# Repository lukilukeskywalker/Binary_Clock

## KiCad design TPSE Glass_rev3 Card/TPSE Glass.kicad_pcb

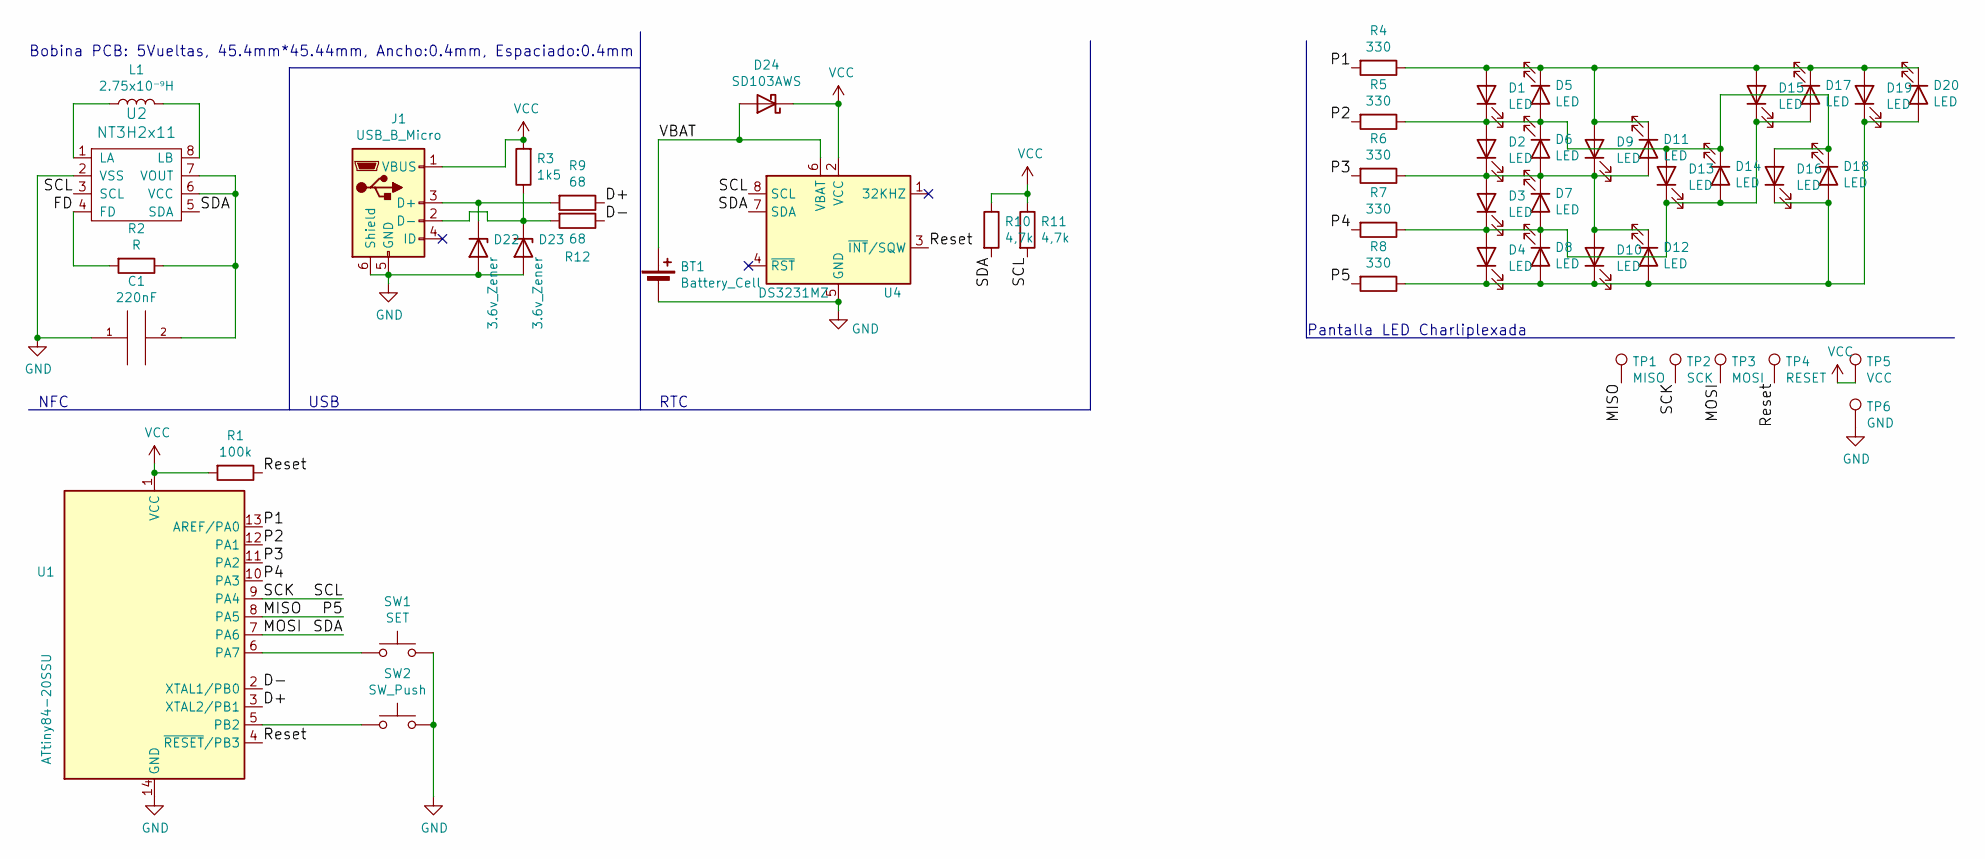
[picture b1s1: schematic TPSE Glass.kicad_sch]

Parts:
BT1: Battery_Cell; TE_796136-1
C1: 220nF; C_1210_3225Metric_Pad1.42x2.65mm_HandSolder
D1, D2, D3, D4, D5, D6, D7, D8, D9, D10, D11, D12, D13, D14, D15, D16, D17, D18, D19, D20: LED; LED_1206_3216Metric-ThroughPCB
D22, D23: 3.6v_Zener; D_SMA
D24: SD103AWS; D_SMA
J1: USB_B_Micro; TE_1981568-1
L1: 2.75x10⁻⁹H
R1: 100k; R_1206_3216Metric
R2: R; R_1206_3216Metric
R3: 1k5; R_1206_3216Metric
R4, R5, R6, R7, R8: 330; R_1206_3216Metric
R9, R12: 68; R_1206_3216Metric
R10, R11: 4,7k; R_1206_3216Metric
SW1: SET; SW_PTS526_SM08_SMTR2_LFS
SW2: SW_Push; SW_PTS526_SM08_SMTR2_LFS
TP1: MISO; TestPoint_Pad_D1.5mm
TP2: SCK; TestPoint_Pad_D1.5mm
TP3: MOSI; TestPoint_Pad_D1.5mm
TP4: RESET; TestPoint_Pad_D1.5mm
TP5: VCC; TestPoint_Pad_D1.5mm
TP6: GND; TestPoint_Pad_D1.5mm
U1: ATtiny84-20SSU; SOIC-14_3.9x8.7mm_P1.27mm
U2: NT3H2x11; TSSOP-8_3x3mm_P0.65mm
U4: DS3231MZ; SOIC-8_3.9x4.9mm_P1.27mm

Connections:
/D+: R9.1, U1.3 (XTAL2/PB1)
/D-: R12.1, U1.2 (XTAL1/PB0)
/FD: R2.2, U2.4 (FD)
/MISO: R8.2, TP1.1, U1.8 (PA5)
/MOSI: R10.2, TP3.1, U1.7 (PA6), U2.5 (SDA), U4.7 (SDA)
/P1: R4.2, U1.13 (AREF/PA0)
/P2: R5.2, U1.12 (PA1)
/P3: R6.2, U1.11 (PA2)
/P4: R7.2, U1.10 (PA3)
/Reset: R1.1, TP4.1, U1.4 (~RESET/PB3), U4.3 (~INT/SQW)
/SCK: R11.2, TP2.1, U1.9 (PA4), U2.3 (SCL), U4.8 (SCL)
/VBAT: BT1.1 (+), D24.2 (A), U4.6 (VBAT)
GND: BT1.2 (-), C1.1, D22.2 (A), D23.2 (A), J1.5 (GND), J1.6 (Shield), SW1.2, SW2.2, TP6.1, U1.14 (GND), U2.2 (VSS), U4.5 (GND)
unnamed: C1.2, R2.1, U2.6 (VCC), U2.7 (VOUT)
unnamed: D1.1 (K), D2.2 (A), D5.2 (A), D6.1 (K), D13.2 (A), D14.1 (K), D16.2 (A), D18.1 (K), R5.1
unnamed: D1.2 (A), D5.1 (K), D9.2 (A), D11.1 (K), D15.2 (A), D17.1 (K), D19.2 (A), D20.1 (K), R4.1
unnamed: D4.1 (K), D8.2 (A), D10.1 (K), D12.2 (A), D16.1 (K), D18.2 (A), D19.1 (K), D20.2 (A), R8.1
unnamed: D2.1 (K), D3.2 (A), D6.2 (A), D7.1 (K), D9.1 (K), D10.2 (A), D11.2 (A), D12.1 (K), R6.1
unnamed: D3.1 (K), D4.2 (A), D7.2 (A), D8.1 (K), D13.1 (K), D14.2 (A), D15.1 (K), D17.2 (A), R7.1
unnamed: D22.1 (K), J1.3 (D+), R9.2
unnamed: D23.1 (K), J1.2 (D-), R3.1, R12.2
unnamed: L1.1, U2.1 (LA)
unnamed: L1.2, U2.8 (LB)
unnamed: SW1.1, U1.6 (PA7)
unnamed: SW2.1, U1.5 (PB2)
VCC: D24.1 (K), J1.1 (VBUS), R1.2, R3.2, R10.1, R11.1, TP5.1, U1.1 (VCC), U4.2 (VCC)

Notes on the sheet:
Bobina PCB: 5Vueltas, 45.4mm*45.44mm, Ancho:0.4mm, Espaciado:0.4mm
NFC
USB
Pantalla LED Charliplexada
RTC

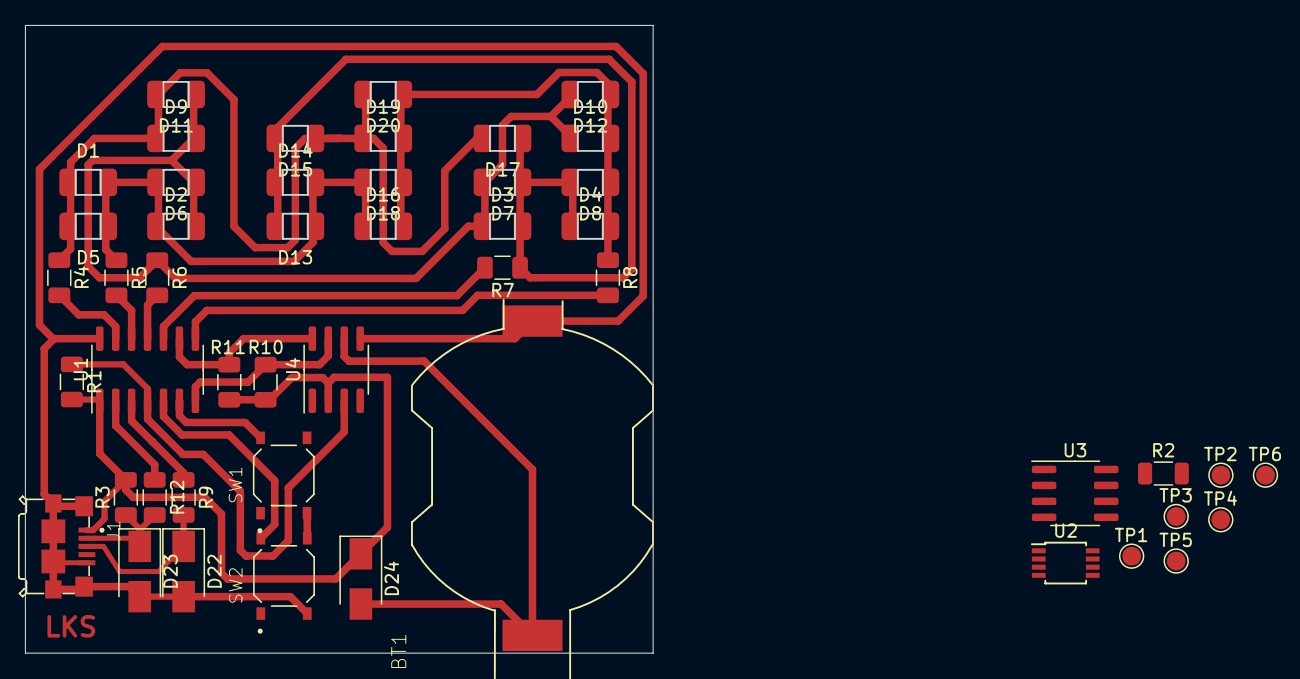
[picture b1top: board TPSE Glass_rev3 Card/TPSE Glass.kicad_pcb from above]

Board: 2 copper layers, 50.0 x 50.0 mm, 49 parts (0 on the bottom side), 24 nets.

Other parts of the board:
U3: PCF8563T; SOIC-8_3.9x4.9mm_P1.27mm

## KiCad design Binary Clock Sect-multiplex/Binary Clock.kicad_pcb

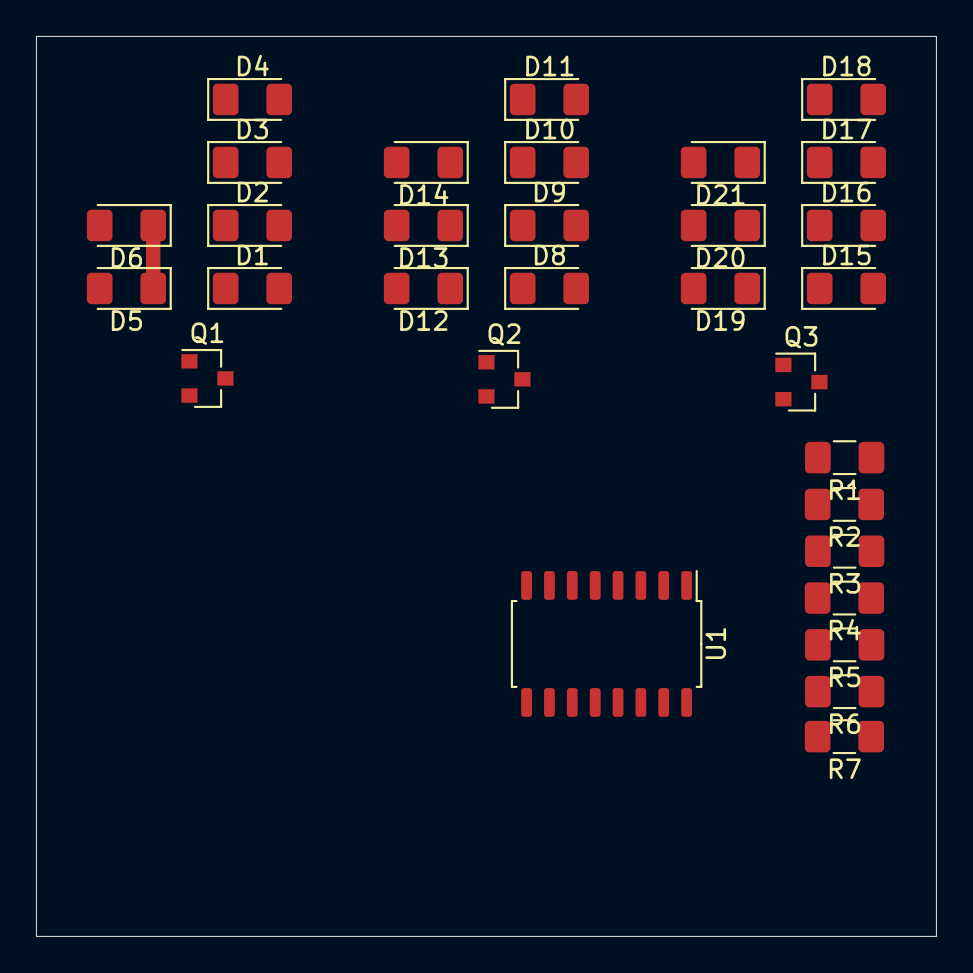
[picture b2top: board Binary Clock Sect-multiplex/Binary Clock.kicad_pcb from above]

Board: 2 copper layers, 50.0 x 50.0 mm, 31 parts (0 on the bottom side), 18 nets.

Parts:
D1, D2, D3, D4, D5, D6, D8, D9, D10, D11, D12, D13, D14, D15, D16, D17, D18, D19, D20, D21: LED; LED_1206_3216Metric_Pad1.42x1.75mm_HandSolder
Q1, Q2, Q3: BC847; SOT-23
R1, R2, R3, R4, R5, R6, R7: R; R_1206_3216Metric_Pad1.42x1.75mm_HandSolder
U1: 74HC595; SOP-16_4.55x10.3mm_P1.27mm

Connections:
/L0: D1.2, D8.2, D15.2, R1.1
/L1: D2.2, D9.2, D16.2, R2.1
/L2: D3.2, D10.2, D17.2, R3.1
/L3: D4.2, D11.2, D18.2, R4.1
/L4: D5.2, D12.2, D19.2, R5.1
/L5: D6.2, D13.2, D20.2, R6.1
/L6: D14.2, D21.2, R7.1
GND: Q1.2, Q2.2, Q3.2, U1.8
unnamed: D1.1, D2.1, D3.1, D4.1, D5.1, D6.1, Q1.3
unnamed: D8.1, D9.1, D10.1, D11.1, D12.1, D13.1, D14.1, Q2.3
unnamed: D15.1, D16.1, D17.1, D18.1, D19.1, D20.1, D21.1, Q3.3
unnamed: R1.2, U1.15
unnamed: R2.2, U1.1
unnamed: R3.2, U1.2
unnamed: R4.2, U1.3
unnamed: R5.2, U1.4
unnamed: R6.2, U1.5
unnamed: R7.2, U1.6

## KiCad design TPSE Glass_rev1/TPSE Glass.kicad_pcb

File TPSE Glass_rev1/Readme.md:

# Revision 1 Details

uC: Atmega32u4
RTC: DS3231 16-SOIC

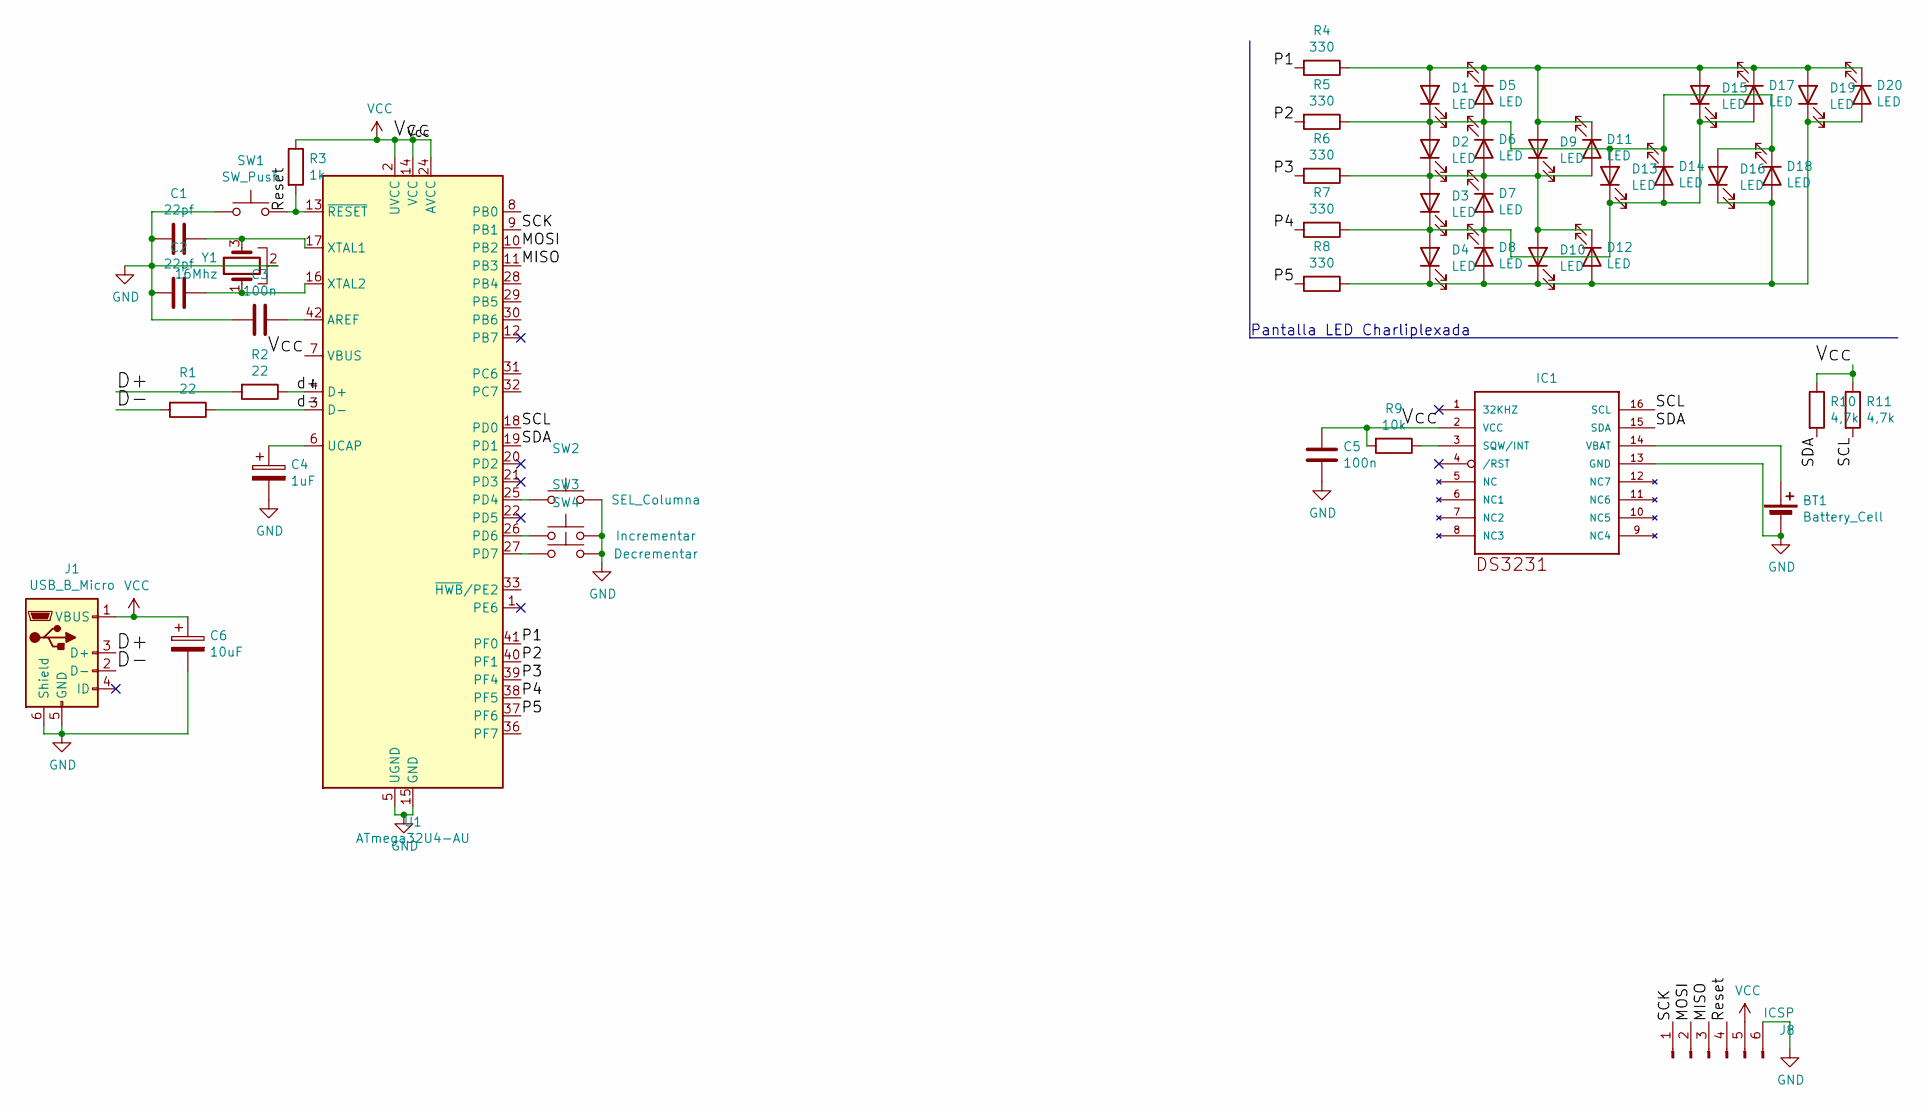
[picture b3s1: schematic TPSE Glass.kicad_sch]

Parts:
BT1: Battery_Cell; LINX CR2032 Holder
C1, C2: 22pf; C_0805_2012Metric_Pad1.15x1.40mm_HandSolder
C3, C5: 100n; C_0805_2012Metric
C4: 1uF; C_0603_1608Metric_Pad1.05x0.95mm_HandSolder
C6: 10uF; CP_EIA-1608-08_AVX-J
D1, D2, D3, D4, D5, D6, D7, D8, D9, D10, D11, D12, D13, D14, D15, D16, D17, D18, D19, D20: LED; LED_1206_3216Metric
IC1: DS3231; SO16W
J1: USB_B_Micro; USB_Micro-B_Molex_47346-0001
J8: ICSP; ICSP_SMD_Conn
R1, R2: 22; R_1206_3216Metric
R3: 1k; R_1206_3216Metric
R4, R5, R6, R7, R8: 330; R_1206_3216Metric
R9: 10k; R_1206_3216Metric
R10, R11: 4,7k; R_1206_3216Metric
SW1: SW_Push; SW_PTS526_SM08_SMTR2_LFS
SW2: SEL_Columna; SW_PTS526_SM08_SMTR2_LFS
SW3: Incrementar; SW_PTS526_SM08_SMTR2_LFS
SW4: Decrementar; SW_PTS526_SM08_SMTR2_LFS
U1: ATmega32U4-AU; TQFP-44_10x10mm_P0.8mm
Y1: 16Mhz; Crystal_SMD_2016-4Pin_2.0x1.6mm

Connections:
/D+: J1.3 (D+), R2.2
/D-: J1.2 (D-), R1.2
/MISO: J8.3, U1.11 (PB3)
/MOSI: J8.2, U1.10 (PB2)
/P1: R4.2, U1.41 (PF0)
/P2: R5.2, U1.40 (PF1)
/P3: R6.2, U1.39 (PF4)
/P4: R7.2, U1.38 (PF5)
/P5: R8.2, U1.37 (PF6)
/Reset: J8.4, R3.2, SW1.2, U1.13 (~RESET)
/SCK: J8.1, U1.9 (PB1)
/SCL: IC1.16 (SCL), R11.2, U1.18 (PD0)
/SDA: IC1.15 (SDA), R10.2, U1.19 (PD1)
/d+: R2.1, U1.4 (D+)
/d-: R1.1, U1.3 (D-)
GND: BT1.2 (-), C1.2, C2.2, C3.2, C4.2, C5.2, C6.2, IC1.13 (GND), J1.5 (GND), J1.6 (Shield), J8.6, SW1.1, SW2.2, SW3.2, SW4.2, U1.5 (UGND), U1.15 (GND), U1.23 (GND), U1.35 (GND), U1.43 (GND), Y1.2
unnamed: BT1.1 (+), IC1.14 (VBAT)
unnamed: C1.1, U1.17 (XTAL1), Y1.3
unnamed: C2.1, U1.16 (XTAL2), Y1.1
unnamed: C3.1, U1.42 (AREF)
unnamed: C4.1, U1.6 (UCAP)
unnamed: D1.1 (K), D2.2 (A), D5.2 (A), D6.1 (K), D13.2 (A), D14.1 (K), D16.2 (A), D18.1 (K), R5.1
unnamed: D1.2 (A), D5.1 (K), D9.2 (A), D11.1 (K), D15.2 (A), D17.1 (K), D19.2 (A), D20.1 (K), R4.1
unnamed: D4.1 (K), D8.2 (A), D10.1 (K), D12.2 (A), D16.1 (K), D18.2 (A), D19.1 (K), D20.2 (A), R8.1
unnamed: D2.1 (K), D3.2 (A), D6.2 (A), D7.1 (K), D9.1 (K), D10.2 (A), D11.2 (A), D12.1 (K), R6.1
unnamed: D3.1 (K), D4.2 (A), D7.2 (A), D8.1 (K), D13.1 (K), D14.2 (A), D15.1 (K), D17.2 (A), R7.1
unnamed: IC1.3 (SQW/INT), R9.1
unnamed: SW2.1, U1.25 (PD4)
unnamed: SW3.1, U1.26 (PD6)
unnamed: SW4.1, U1.27 (PD7)
VCC: C5.1, C6.1, IC1.2 (VCC), J1.1 (VBUS), J8.5, R3.1, R9.2, R10.1, R11.1, U1.2 (UVCC), U1.7 (VBUS), U1.14 (VCC), U1.24 (AVCC), U1.34 (VCC), U1.44 (AVCC)

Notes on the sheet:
Pantalla LED Charliplexada

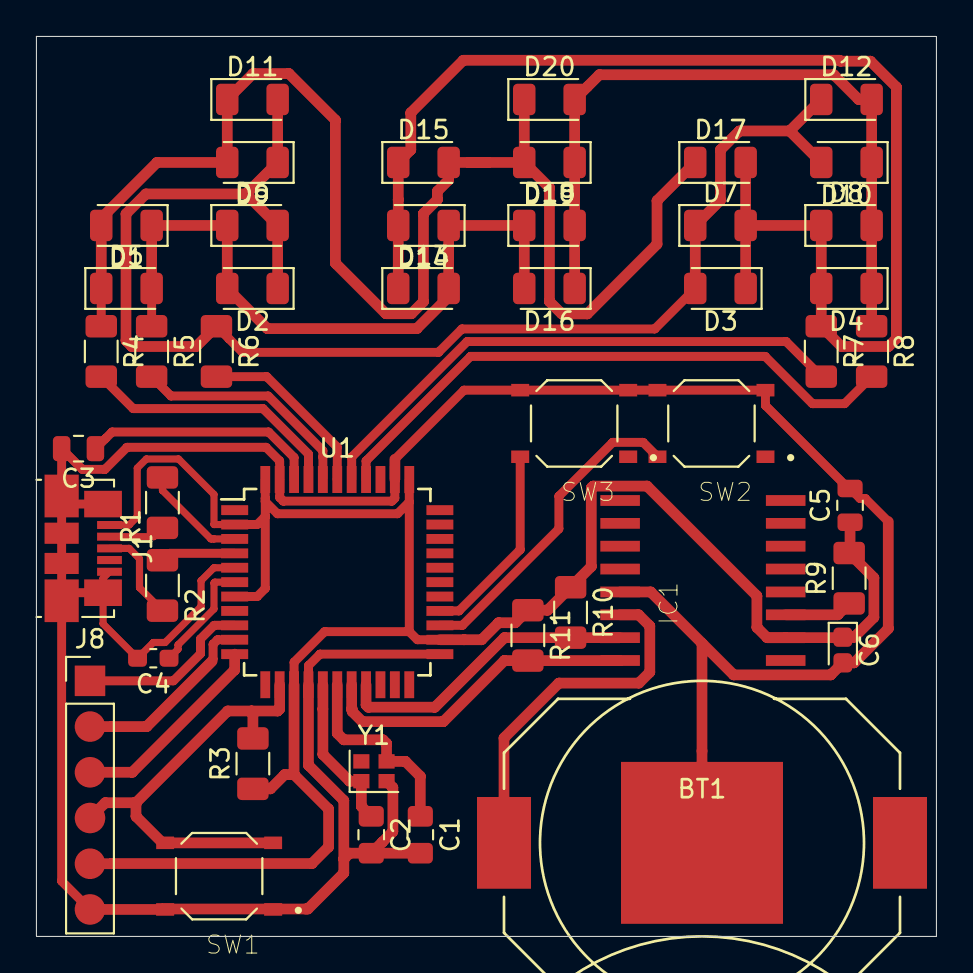
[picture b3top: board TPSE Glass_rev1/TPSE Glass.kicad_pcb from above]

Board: 2 copper layers, 50.0 x 50.0 mm, 46 parts (0 on the bottom side), 30 nets.

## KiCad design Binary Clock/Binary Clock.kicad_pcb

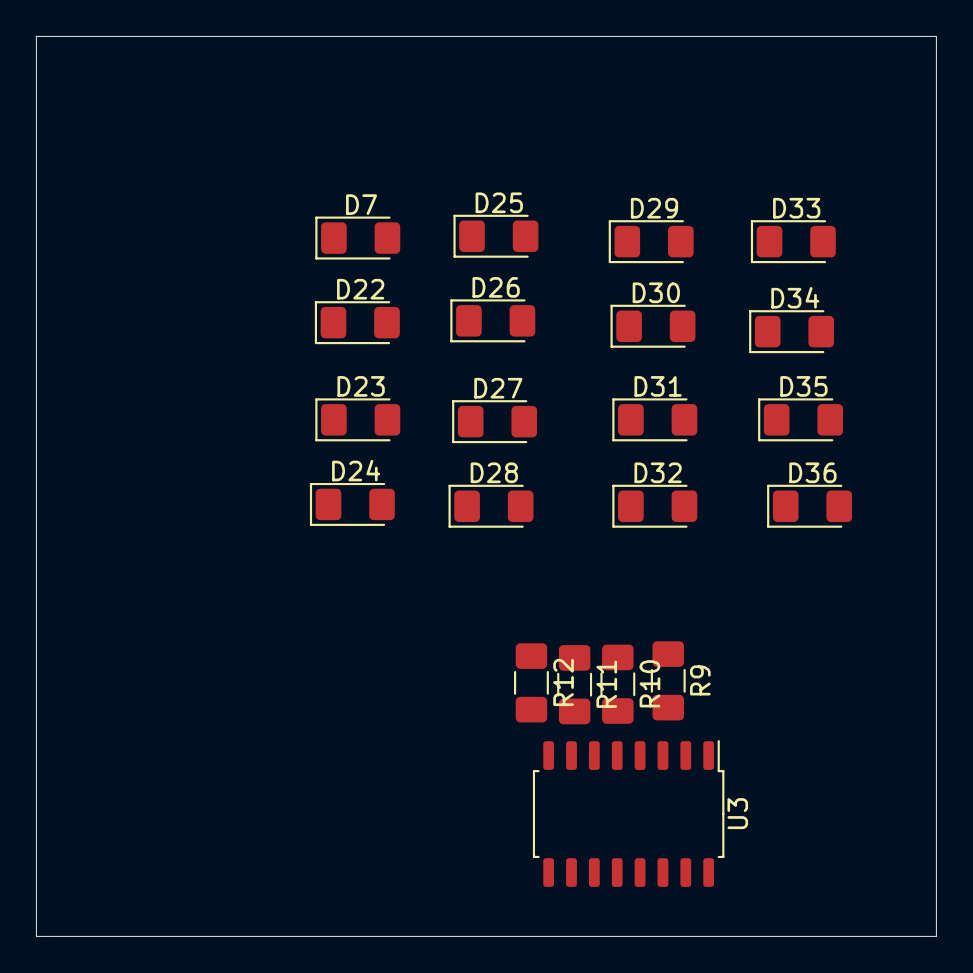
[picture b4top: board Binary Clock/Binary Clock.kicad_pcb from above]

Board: 2 copper layers, 50.0 x 50.0 mm, 21 parts (0 on the bottom side), 12 nets, no tracks yet.

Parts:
D7, D22, D23, D24, D25, D26, D27, D28, D29, D30, D31, D32, D33, D34, D35, D36: LED; LED_1206_3216Metric_Pad1.42x1.75mm_HandSolder
R9, R10, R11, R12: R; R_1206_3216Metric_Pad1.42x1.75mm_HandSolder
U3: 74HC595; SOP-16_4.55x10.3mm_P1.27mm

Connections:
/Col0: D7.2, D22.2, D23.2, D24.2, U3.15
/Col1: D25.2, D26.2, D27.2, D28.2, U3.1
/Col2: D29.2, D30.2, D31.2, D32.2, U3.2
/Col3: D33.2, D34.2, D35.2, D36.2, U3.3
/Fil0: D7.1, D25.1, D29.1, D33.1, R9.1
/Fil1: D22.1, D26.1, D30.1, D34.1, R10.1
/Fil2: D23.1, D27.1, D31.1, D35.1, R11.1
/Fil3: D24.1, D28.1, D32.1, D36.1, R12.1
unnamed: R9.2, U3.4
unnamed: R10.2, U3.5
unnamed: R11.2, U3.6
unnamed: R12.2, U3.7

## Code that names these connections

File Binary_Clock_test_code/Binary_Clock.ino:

  //LED DRIVERS DEFINITIONS
//int led_pins[]={PINF0, PINF1, PINF4, PINF6};
#include <avr/wdt.h>
//#include <DS3231.h>

#if defined(ARDUINO_AVR_MICRO)
#include <Wire.h>
const int led_pins[]={A5, A4, A3, A2, A1};  // P1, P2, P3, P4, P5
//int Horas_pins[]={A5, A4, A3};
//int Minutos_pins[]={A2, A4, A1};  //Este caso es complejo. La parte superior no se selecciona, con el 1 pin, sino con un cuarto. P1, A5. Ademas selecciona la seccion alta del segundo segmento.
//int Segundos_pins[]={A3, A2, A1};
//int Agrupacion_M[]={A5, A2, A4, A5, A4, A2};
//int Agrupacion_S[]={A5, A2, A3, A3, A2, A1};
#elif defined(__AVR_ATtiny84__)
#include <USIWire.h>
int led_pins[]={0, 1, 2, 3, 5};  // P1, P2, P3, P4, P5 //Attiny84 Positions PORTA0, PORTA1, PORTA2, PORTA3, PORTA5
#define BUTTONS 7 //I think I will look for the button pressed by toggling the led_pins 
#define SET_PIN led_pins[0]
#define SELECT_PIN led_pins[1]
#endif
#define TIMESET_TIMEOUT 60    //60 seconds to make a change.
int Horas_pins[]={led_pins[0], led_pins[1], led_pins[2]};
int Minutos_pins[]={led_pins[0], led_pins[1], led_pins[4]};
int Segundos_pins[]={led_pins[2], led_pins[3], led_pins[4]};
int Agrupacion_H[]={led_pins[0],led_pins[1],led_pins[2],led_pins[0],led_pins[1],led_pins[2]};
int Agrupacion_M[]={led_pins[0],led_pins[3],led_pins[1], led_pins[0], led_pins[1], led_pins[4]};
int Agrupacion_S[]={led_pins[0],led_pins[3],led_pins[2],led_pins[2],led_pins[3],led_pins[4]};

//#include <RtcDS3231.h>
//RtcDS3231<TwoWire> Rtc(Wire);
//DS3231 Clock;
struct time_struct{
  uint8_t hour;
  uint8_t minute;
  uint8_t second;
};
time_struct time;
unsigned long time_elapsed=0;
byte set_button_counter=0;
byte change_pos=0;
void setup() {
  //wdt_disable();
  Wire.begin();
  DS3231_init();
  //Rtc.Begin();
  DS3231_get_time(&time);
}
void setPin(int pin, bool state){
  DDRA |= (0X01 << pin);
  PORTA |= (state << pin);
}
void printHoras(byte numero, int* pines, bool not_minutes, bool horas){
  //El booleano not_minutes se usa en el 3 led del segundo segmento, para determinar que lado de los 2 es (Minutos o segundos)
  byte primer_digito = numero & 0x0F;//numero%10; //Guardamos el primer digito
  byte segundo_digito = (numero>>4)&0x0F;//numero/10;//Guardamos el segundo digito
  int length = 5;//(sizeof(pines)/sizeof(pines[0]))-1;//5;//sizeof(pines);
  if(horas) length=2;
  for(int i=0; i<4; i++){
    if((primer_digito>>i)&0x01){
      pinMode(pines[length], OUTPUT); //Lo pongo en en OUTPUT, porque esta seccion del segmento sera la que manejemos prmero.
      //Estos son los casos para la primera parte del segmento, que esta controlada por la ultima patilla en el array
      ////Serial.println(String("Comprobacion Realizada Bit numero: ")+i+String("Byte: ")+ primer_digito);
      switch(i){
        case 0:
          /*digitalWrite(pines[length], HIGH);
          pinMode(pines[length-1], OUTPUT);
          digitalWrite(pines[length-1], LOW);*/
          setPin(pines[length], 1);
          setPin(pines[length-1], 0);
          break;
        case 1:
          /*digitalWrite(pines[length], LOW);
          pinMode(pines[length-1], OUTPUT);
          digitalWrite(pines[length-1], HIGH);*/
          setPin(pines[length], 0);
          setPin(pines[length-1], 1);
          break;
        case 2:
          /*digitalWrite(pines[length], HIGH);
          pinMode(pines[length-2], OUTPUT);
          digitalWrite(pines[length-2], LOW);*/
          setPin(pines[length], 1);
          setPin(pines[length-2], 0);
          break;
        case 3:
          /*digitalWrite(pines[length], LOW);
          pinMode(pines[length-2], OUTPUT);
          digitalWrite(pines[length-2], HIGH);*/
          setPin(pines[length], 0);
          setPin(pines[length-2], 1);
          break;
      }
      delay(1);
      PORTA= PORTA & B01010000;//0x00;
      DDRA = DDRA & B01010000;//0x00;
      
    }
    if((segundo_digito>>i)&0x01){
      ////Serial.println(String("Comprobacion Realizada Bit numero: ")+i+String("Byte: ")+ segundo_digito);
      switch(i){
        case 0:
          if(horas){
            //pinMode(pines[0], OUTPUT);
            //pinMode(pines[1], OUTPUT);
            //digitalWrite(pines[0], HIGH);
            //digitalWrite(pines[1], LOW);
            setPin(pines[0], 1);
            setPin(pines[1], 0);
          }else{
            /*pinMode(pines[length-3], OUTPUT);
            pinMode(pines[length-4], OUTPUT);
            digitalWrite(pines[length-3], LOW);
            digitalWrite(pines[length-4], HIGH);*/
            setPin(pines[length-3], 0);
            setPin(pines[length-4], 1);
          }
          break;
        case 1:
          if(horas){
            /*pinMode(pines[0], OUTPUT);
            pinMode(pines[1], OUTPUT);
            digitalWrite(pines[0], LOW);
            digitalWrite(pines[1], HIGH);*/
            setPin(pines[0], 0);
            setPin(pines[1], 1);
          }
          else{
            /*pinMode(pines[length-3], OUTPUT);
            pinMode(pines[length-4], OUTPUT);
            digitalWrite(pines[length-3], HIGH);
            digitalWrite(pines[length-4], LOW);*/
            setPin(pines[length-3], 1);
            setPin(pines[length-4], 0);
          }
          break;
        case 2:
          /*pinMode(pines[length-4], OUTPUT);
          pinMode(pines[length-5], OUTPUT);
          digitalWrite(pines[length-4], not_minutes);
          digitalWrite(pines[length-5], !not_minutes);*/
          setPin(pines[length-4], not_minutes);
          setPin(pines[length-5], !not_minutes);
          break;
      }
      delay(1);
      PORTA= PORTA & B01010000;//0x00;
      DDRA = DDRA & B01010000;//0x00; //Excluimos los pines de I2C
    }

  }
}
void PbcdCounter(struct time_struct *t){
  //Positive Binary coded decimal counter. In this program, each byte has 2 decimals. Internet examples use only one per byte... such a waste in memory space
  //Lets try this only with seconds first...
  t->second++;
  //byte contra = (number & 0xF0)+0x0A;
  if(!((t->second&0x0F)^0x0A)){//if(!((number^0x0A)<<5)){//if(!((number&0x0F)^0x0A)){//if(!(number^contra)){
     t->second=(t->second&0xF0)+0x10;
     if(!((t->second&0xF0)^0x60)){
      t->second=0;
      t->minute++;
      if(!((t->minute&0x0F)^0x0A)){//if(!((number^0x0A)<<5)){//if(!((number&0x0F)^0x0A)){//if(!(number^contra)){
        t->minute=(t->minute&0xF0)+0x10;
        if(!((t->minute&0xF0)^0x60)){
          t->minute=0;
          t->hour++;
          if(!((t->hour&0x0F)^0x0A)){
            t->hour=(t->hour&0x30)+0x10;
          }
          else if(t->hour==0x24){
            t->hour=0;
          }
        }
      }
     }
  }
  /*if(((t->second&0x08)!=0x00)&&(t->second&0x02)!=0x00){
    t->second=(t->second&0xF0)+0x10;
  }*/
  //return number;
}

void loop() {
  //A ver... Los pines de los leds son el PFO, PF1, PF4, PF5, PF6. Con solo 5 pines podemos charliplexar 20 Leds. Ahora solo hay que conseguir escribir el codigo.
  //Con el registrp DDX, en este caso DDF, seleccionamos si deseamos el pin en estado salida o entrada. Si queremos que tenga una alta impedancia, lo seleccionamos a entrada, poniendolo
  //en  0, o en 1 si lo queremos como salida. 
  //En el registro PORTX, selecionamos el estado. Osea HIGH o LOW
  if(time.minute%10==0 && time.second==0){
    //Wire.begin();
    DS3231_get_time(&time);
  }
//  if(set_button_pressed()){
//    set_button_counter++;
//    unsigned long start=millis();
//    while(millis()>(start+TIMESET_TIMEOUT*1000)&set_button_counter==5){ //If the set button has been pressed for 5 secs, it enters into programming mode.
//      while(millis()-time_elapsed<1000){
//        printHoras(time.hour, Horas_pins, false, true);
//        printHoras(time.minute, Agrupacion_M, true, false);
//        printHoras(time.second, Agrupacion_S, false, false);
//        
//        }
//        time_elapsed=millis();
//        time.second++;
//        if (time.second ==60){
//          time.second=0;
//        }
//    }
//  }
//  else{
//    set_button_counter=0;
//  }
  selfsetHour();
  if(select_button_pressed()){
    int temperature=DS3231_get_temp();
    while(select_button_pressed()){
      printHoras(((temperature&0xFF00)>>8), Agrupacion_M, true, false);
      printHoras((temperature&0x00FF), Agrupacion_S, false, false);
      //printHoras((temperature), Agrupacion_M, true, false);
    }
  }
  while(millis()-time_elapsed<1000){
    printHoras(time.hour, Horas_pins, false, true);
    printHoras(time.minute, Agrupacion_M, true, false);
    printHoras(time.second, Agrupacion_S, false, false);
  }
  time_elapsed=millis();
  //time.second++;
  PbcdCounter(&time);
  /*if (time.second ==60){
    time.second=0;
    time.minute++;
    if(time.minute==60){
      time.minute=0;
      time.hour++;
      if(time.hour==24){
        time.hour=0;
        }
      }
    }*/
}

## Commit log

2022-12-13 [Board][Code]Preliminary commit, needs refactoring
2023-11-28 [Cleanup]
2023-11-28 [Code]Test code
